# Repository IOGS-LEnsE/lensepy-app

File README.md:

# lensepy-app
Application developped by the LEnsE

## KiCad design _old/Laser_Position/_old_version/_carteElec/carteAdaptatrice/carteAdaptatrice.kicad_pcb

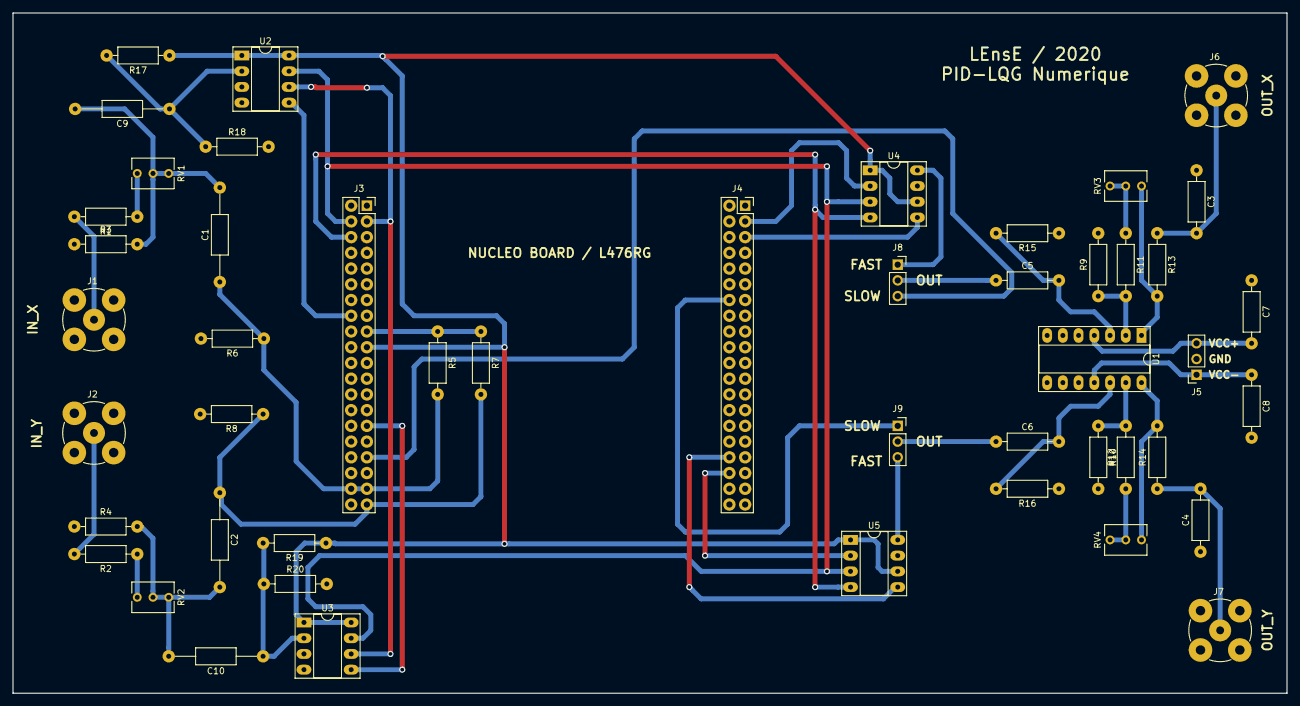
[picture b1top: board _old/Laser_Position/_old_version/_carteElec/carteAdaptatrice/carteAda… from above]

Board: 2 copper layers, 205.7 x 109.9 mm, 48 parts (0 on the bottom side), 40 nets.

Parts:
C1, C2, C9, C10: 100uF; R_Axial_DIN0207_L6.3mm_D2.5mm_P15.24mm_Horizontal
C3, C4: Cf; R_Axial_DIN0207_L6.3mm_D2.5mm_P10.16mm_Horizontal
C5, C6: CfHP; R_Axial_DIN0207_L6.3mm_D2.5mm_P10.16mm_Horizontal
C7, C8: 100n; R_Axial_DIN0207_L6.3mm_D2.5mm_P10.16mm_Horizontal
J1: IN_X; BNC_TEConnectivity_1478204_Vertical
J2: IN_Y; BNC_TEConnectivity_1478204_Vertical
J3: MORPHO_GAUCHE; PinSocket_2x20_P2.54mm_Vertical
J4: MORPHO_DROITE; PinSocket_2x20_P2.54mm_Vertical
J5: ALIM; PinSocket_1x03_P2.54mm_Vertical
J6: OUT_X; BNC_TEConnectivity_1478204_Vertical
J7: OUT_Y; BNC_TEConnectivity_1478204_Vertical
J8, J9: Conn_01x03; PinSocket_1x03_P2.54mm_Vertical
R1, R2: 18k; R_Axial_DIN0207_L6.3mm_D2.5mm_P10.16mm_Horizontal
R3, R4: 6.8k; R_Axial_DIN0207_L6.3mm_D2.5mm_P10.16mm_Horizontal
R5, R6, R7, R8, R17, R18, R19, R20: 100k; R_Axial_DIN0207_L6.3mm_D2.5mm_P10.16mm_Horizontal
R9, R10: 10k; R_Axial_DIN0207_L6.3mm_D2.5mm_P10.16mm_Horizontal
R11, R12: 47k; R_Axial_DIN0207_L6.3mm_D2.5mm_P10.16mm_Horizontal
R13, R14: Rf; R_Axial_DIN0207_L6.3mm_D2.5mm_P10.16mm_Horizontal
R15, R16: RfHP; R_Axial_DIN0207_L6.3mm_D2.5mm_P10.16mm_Horizontal
RV1, RV2, RV3, RV4: 10k; Potentiometer_Vishay_T73XW_Horizontal
U1: TL084; DIP-14_W7.62mm_Socket_LongPads
U2, U3: MCP3201; DIP-8_W7.62mm_Socket_LongPads
U4, U5: MCP4921; DIP-8_W7.62mm_Socket_LongPads

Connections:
3.3V: J3.17, R5.1, R7.1
5V: J3.19, R17.1, R19.1, U2.1, U2.8, U3.1, U3.8, U4.1, U4.6, U5.1, U5.6
CS_ADC1: J3.16, U2.5
CS_ADC2: J3.29, U3.5
CS_DAC1: J4.3, U4.2
CS_DAC2: J4.36, U5.2
GND: C3.1, C4.1, C7.1, C8.2, J1.2, J2.2, J3.21, J3.22, J3.23, J5.2, J6.2, J7.2, R3.1, R4.1, R6.2, R8.2, R9.2, R10.2, R15.1, R16.1, R18.2, R20.2, U2.3, U2.4, U3.3, U3.4, U4.7, U5.7
LDAC1: J4.5, U4.5
LDAC2: J4.34, U5.5
MISO: J3.3, U2.6, U3.6
MOSI: J3.6, U4.4, U5.4
unnamed: C3.2, J6.1, R13.1
unnamed: C4.2, J7.1, R14.1
unnamed: C5.1, J8.2
unnamed: C5.2, R15.2, U1.3
unnamed: C6.1, J9.2
unnamed: C6.2, R16.2, U1.12
unnamed: C9.1, R17.2, R18.1, U2.2
unnamed: C10.1, R19.2, R20.1, U3.2
unnamed: J1.1, R1.2
unnamed: J2.1, R2.2
unnamed: R1.1, RV1.3
unnamed: R2.1, RV2.3
unnamed: R10.1, R12.2, U1.13
unnamed: R11.1, RV3.1, RV3.2
unnamed: R9.1, R11.2, U1.2
unnamed: R12.1, RV4.1, RV4.2
unnamed: R13.2, RV3.3, U1.1
unnamed: R14.2, RV4.3, U1.14
SCK: J3.4, U2.7, U3.7, U4.3, U5.3
VCC+: C7.2, J5.3, U1.4
VCC-: C8.1, J5.1, U1.11
V_IN_X: C1.1, J3.37, J3.38, R5.2, R6.1
V_IN_X_5: C1.2, C9.2, R3.2, RV1.1, RV1.2
V_IN_Y: C2.1, J3.39, R7.2, R8.1
V_IN_Y_5: C2.2, C10.2, R4.2, RV2.1, RV2.2
V_OUT_X: J3.33, J8.3
V_OUT_X_DAC: J8.1, U4.8
V_OUT_Y: J4.14, J9.1
V_OUT_Y_DAC: J9.3, U5.8

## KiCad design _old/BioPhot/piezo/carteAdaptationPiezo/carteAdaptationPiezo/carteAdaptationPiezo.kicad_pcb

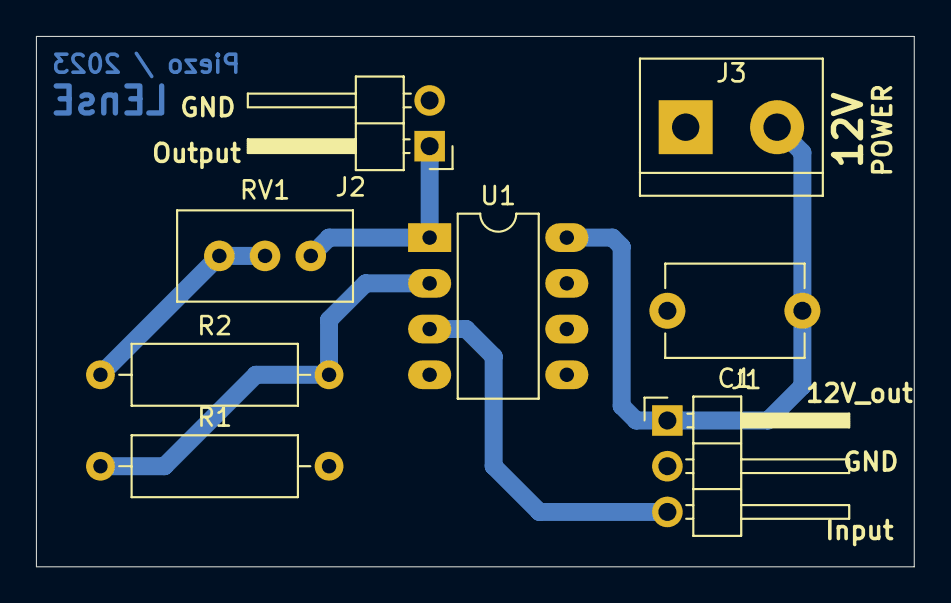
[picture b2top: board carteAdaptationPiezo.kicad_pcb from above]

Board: 2 copper layers, 48.8 x 29.5 mm, 8 parts (0 on the bottom side), 6 nets.

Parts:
C1: 100n; C_Disc_D7.5mm_W5.0mm_P7.50mm
J1: Nucleo; PinHeader_1x03_P2.54mm_Horizontal
J2: Output; PinHeader_1x02_P2.54mm_Horizontal
J3: POWER_IN_12V; TerminalBlock_bornier-2_P5.08mm
R1: 56k; R_Axial_DIN0309_L9.0mm_D3.2mm_P12.70mm_Horizontal
R2: 100k; R_Axial_DIN0309_L9.0mm_D3.2mm_P12.70mm_Horizontal
RV1: 47k Multi; Potentiometer_Bourns_3296W_Vertical
U1: LM358; DIP-8_W7.62mm_LongPads

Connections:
12V: C1.1, J1.1, J3.2, U1.8
GND: C1.2, J1.2, J2.2, J3.1, R1.2, U1.4
unnamed: J1.3, U1.3
unnamed: J2.1, RV1.1, U1.1
unnamed: R1.1, R2.2, U1.2
unnamed: R2.1, RV1.2, RV1.3

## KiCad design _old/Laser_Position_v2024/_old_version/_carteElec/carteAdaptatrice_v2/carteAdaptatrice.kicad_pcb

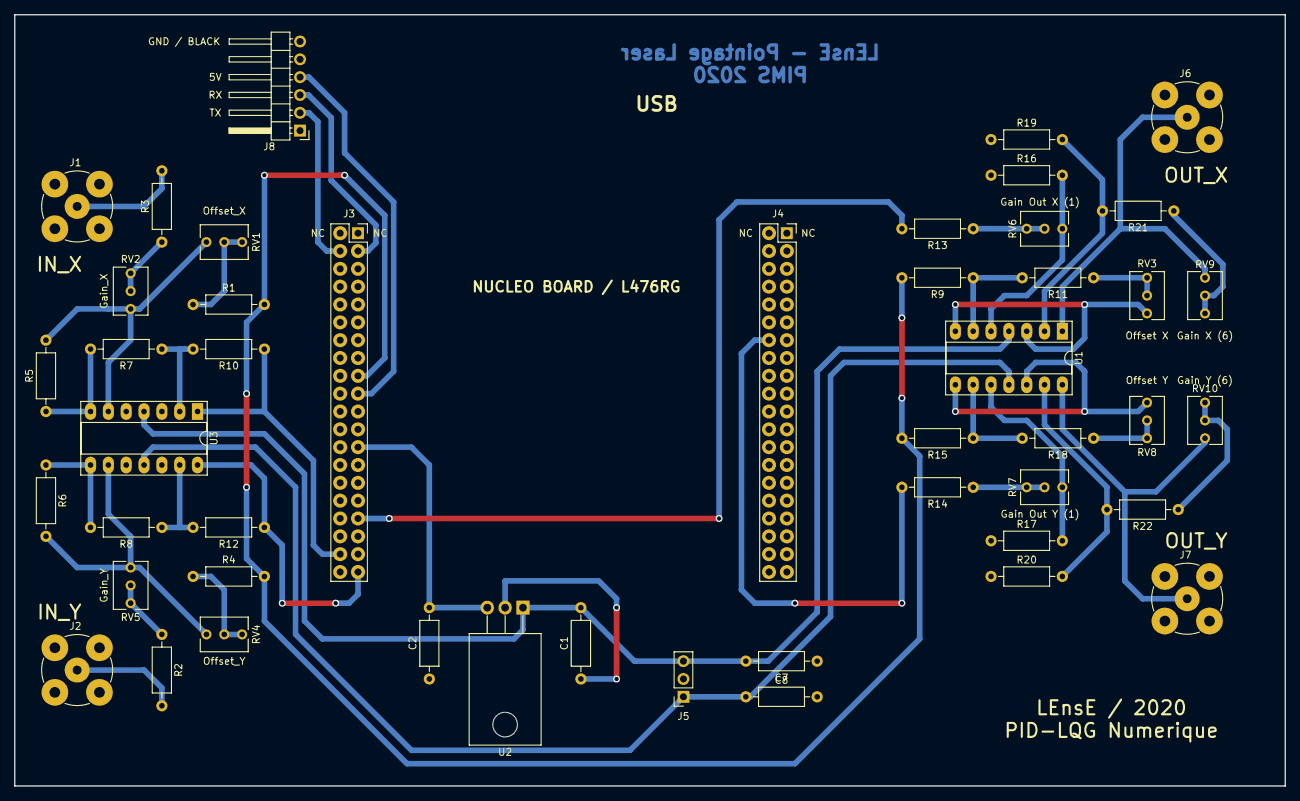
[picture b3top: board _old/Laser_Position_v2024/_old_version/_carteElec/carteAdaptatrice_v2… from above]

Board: 2 copper layers, 181.0 x 109.9 mm, 47 parts (0 on the bottom side), 40 nets.

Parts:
C1, C2: 1u; R_Axial_DIN0207_L6.3mm_D2.5mm_P10.16mm_Horizontal
C7, C8: 100n; R_Axial_DIN0207_L6.3mm_D2.5mm_P10.16mm_Horizontal
J1: IN_X; BNC_TEConnectivity_1478204_Vertical
J2: IN_Y; BNC_TEConnectivity_1478204_Vertical
J3: MORPHO_GAUCHE; PinSocket_2x20_P2.54mm_Vertical
J4: MORPHO_DROITE; PinSocket_2x20_P2.54mm_Vertical
J5: ALIM; PinSocket_1x03_P2.54mm_Vertical
J6: OUT_X; BNC_TEConnectivity_1478204_Vertical
J7: OUT_Y; BNC_TEConnectivity_1478204_Vertical
J8: RS232; PinHeader_1x06_P2.54mm_Horizontal
R1, R4: 1.8k; R_Axial_DIN0207_L6.3mm_D2.5mm_P10.16mm_Horizontal
R2, R3: 12k; R_Axial_DIN0207_L6.3mm_D2.5mm_P10.16mm_Horizontal
R5, R6, R7, R8, R10, R12, R19, R20: 1.2k; R_Axial_DIN0207_L6.3mm_D2.5mm_P10.16mm_Horizontal
R9, R15, R16, R17: 2.2k; R_Axial_DIN0207_L6.3mm_D2.5mm_P10.16mm_Horizontal
R11, R13, R14, R18: 1k; R_Axial_DIN0207_L6.3mm_D2.5mm_P10.16mm_Horizontal
R21, R22: 5.6k; R_Axial_DIN0207_L6.3mm_D2.5mm_P10.16mm_Horizontal
RV1, RV3, RV4, RV6, RV7, RV8, RV9, RV10: 1k; Potentiometer_Vishay_T73XW_Horizontal
RV2, RV5: 4.7k; Potentiometer_Vishay_T73XW_Horizontal
U1, U3: TL084; DIP-14_W7.62mm_Socket_LongPads
U2: L7809; TO-220-3_Horizontal_TabDown

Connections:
3.3V: J3.17, R1.2, R4.2, R9.2, R15.2
5V: J3.19, J8.4
GND: C1.1, C2.1, C7.1, C8.2, J1.2, J2.2, J3.21, J3.22, J3.23, J5.2, J6.2, J7.2, J8.6, R16.1, R17.1, R19.1, R20.1, U2.2, U3.3, U3.5, U3.10, U3.12
unnamed: J1.1, R3.2
unnamed: J2.1, R2.2
unnamed: J6.1, RV9.3, U1.1
unnamed: J7.1, RV10.3, U1.14
unnamed: R1.1, RV1.1, RV1.2
unnamed: R2.1, RV5.1, RV5.2
unnamed: R3.1, RV2.1, RV2.2
unnamed: R4.1, RV4.1, RV4.2
unnamed: R5.1, R7.2, U3.7
unnamed: R5.2, RV1.3, RV2.3, U3.6
unnamed: R6.1, R8.2, U3.8
unnamed: R6.2, RV4.3, RV5.3, U3.9
unnamed: R7.1, R10.2, U3.2
unnamed: R11.1, RV3.1, RV3.2
unnamed: R9.1, R11.2, U1.6
unnamed: R8.1, R12.2, U3.13
unnamed: R13.1, RV6.1, RV6.2
unnamed: R14.1, RV7.1, RV7.2
unnamed: R15.1, R18.2, U1.9
unnamed: R16.2, RV6.3, U1.5
unnamed: R17.2, RV7.3, U1.10
unnamed: R18.1, RV8.1, RV8.2
unnamed: R19.2, R21.2, U1.2
unnamed: R20.2, R22.2, U1.13
unnamed: R21.1, RV9.1, RV9.2
unnamed: R22.1, RV10.1, RV10.2
unnamed: RV3.3, U1.3, U1.7
unnamed: RV8.3, U1.8, U1.12
RX_PC_11: J3.3, J8.3
TX_PC_10: J3.4, J8.2
VCC+: C1.2, C7.2, J5.3, U1.4, U2.1, U3.4
VCC-: C8.1, J5.1, U1.11, U3.11
V_IN_X_PC_2: J3.38, R10.1, U3.1
V_IN_Y_PC_10: J3.39, R12.1, U3.14
V_OUT_X_PA_4: J3.33, R13.2
V_OUT_Y_PA_5: J4.14, R14.2
Vin: C2.2, J3.25, U2.3

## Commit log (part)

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2026-02-27 deploy: c3001f332cb36796825e131978fc9d6823c87354
2026-02-27 Update Project information
2026-02-27 Change file structure
2026-02-27 Update Python package upload workflow
2026-02-27 Update HOM Gui / Coincidence view
2026-02-27 Update HOM Gui / Coincidence View Final version to test
2026-02-28 Update main structure / adding default langage choice (in app and modules)
2026-02-28 Minor update
2026-02-28 Update / standalone app and example / correction on modules
2026-02-28 Update HOM Gui / minor update
2026-03-14 Update Colorimetry GUI / Add Gammut module (to complete)
2026-03-14 Update Colorimetry APP / Web app
2026-03-14 Update Colorimetry GUI / Add Gammut (to complete) and save as image (to complete)
2026-03-14 Update Colorimetry GUI / Save PNG OK in CIE1931 module
2026-03-14 UPdate Colorimetry APP / Adding gamut of screen (to do : add/remove gamut)
2026-03-15 Update Colorimetry GUI / Small upgrade
2026-03-15 Update Colorimetry GUI / small update
2026-03-16 Update HOM Gui / minor updates
2026-03-20 Update HOM Gui / firmware
2026-03-20 Update All BAT applications / Update HOM gui with new modules (quantum_g2)
2026-03-20 Update Zygo app (to complete) / Adding options to start_app (ok)
2026-03-21 Update Zygo v3 lensepy_app / adding images (trouble with masks)
2026-03-22 Update to 1.0.3 / Zygo APP added (to complete) - tested
2026-03-22 Remove Data
2026-03-22 Remove _old
2026-03-22 Update Zygo GUI / adding masks and interferometric control displays
2026-03-22 Update Zygo App / Update 3D view
2026-03-23 Update ZYGO v3
2026-03-23 Update ZYGO / Minor update on Surfaces 2D 3D - save png
2026-03-23 Update ZYGO v3 / Images OK
2026-03-24 Update Quantum Coincidence
2026-03-24 Upate GUIs / Minor update
2026-03-24 Update new_exemple of standalone application
2026-03-24 Move applis to applis_dir
2026-03-24 Update GUIs / Adding contributors + test for IDS camera
2026-03-24 Update Zygo GUI / Adding camera acquisition for IDS
2026-03-25 UPdate Zygo / Add camera control IDS
2026-03-25 Update Zygo Gui / Adding camera and acquisition (to complete)
2026-03-25 Update Zygo App / Add acquisition steps (to test with piezo)
2026-03-26 Update Zygo GUI / 1A version completed (to test with piezo)
    Starting 2A aberrations on images
2026-03-26 Update Zygo Gui / version 2A - test with aberrations
2026-03-26 Update Zygo GUI / Add Simulation for aberrations via Zernike coeffs
2026-03-27 minor updates
2026-03-28 Update Zygo Gui / SImulation
2026-03-29 Add ressources and examples for Zygo aberrations
2026-03-29 Update Zygo App / Adding PSF in simulation
2026-03-30 Update Zygo Gui / Update simulation
2026-03-30 Update docs
2026-03-30 Update Zygo / Add nm-lambda button (to complete) in simulation
2026-03-31 Update Zygo GUI / 2A version - minor updates
2026-03-31 Update Zygo Gui / Still issues with displaying PSF of real date
2026-04-01 Update Zygo GUI 2A / add FTM
2026-04-01 Update ZYgo / display update in simulation
2026-04-02 Update Zygo / Adding circled to simulation
2026-04-02 Update HOM Gui
2026-04-03 Try with camera...
2026-04-03 Adding IDS test (for Python 3.13)
2026-04-10 Adding IDS examples
2026-04-10 Adding IDS camera new test - GOOD = test_ids_peak
    From IDS-peak examples
2026-04-10 Update Zygo App / Adding camera IDS setup and image capture
2026-04-13 Update ZYgo v2A - adding camera
2026-04-14 Update Zygo App / Adding MAT file saving in images module
2026-04-14 Update Zygo Gui / Adding saving MAT file and exposure time management
2026-04-16 Update HOM Gui / Adding correction on coincidence values
2026-05-05 Create Fizo APP / Adding Baslerlite and FFT
2026-05-06 Update FYZO App / Adding FFT and update init camera
2026-05-06 Update Fyzo / Adding FFt in real time and mask
    To do : reconstruction of the surface (and display + PV,RMS)
2026-05-07 Update Fyzo APP / Adding multiview in analysis view
2026-05-07 Update Fyzo App / Adding different view - separate FFT and analysis
2026-05-07 Update Fyzo / Update saving png
2026-06-01 Update Zygo gui / coeff view with gauge
2026-06-01 deploy: 434270388d5c1c5d9defabf5cf7fd15d3ffd7b6f
2026-06-01 Update Zygo App / Adding docs
2026-06-02 Update Zygo / Adding zernike coeffs view (and check)
    To do : update surface display with correction (2 graphes)
2026-06-02 Update Zygo APP 2A / adding correction on zernike view
2026-06-03 Update Zygo Docs
2026-06-03 Update Fizo / lang
2026-06-03 Remove old files
2026-06-03 Update Zygo App / Change downsampling images
2026-06-05 Update Fyzo Gui / update FFT masks
